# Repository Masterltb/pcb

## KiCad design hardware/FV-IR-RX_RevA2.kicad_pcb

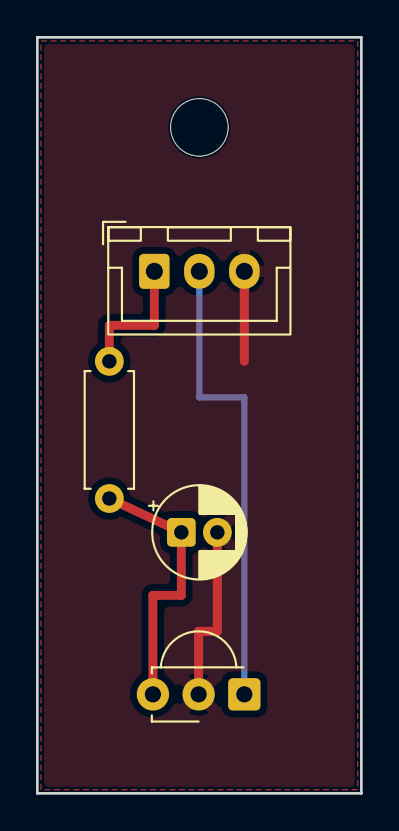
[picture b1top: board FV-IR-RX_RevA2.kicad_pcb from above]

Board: 2 copper layers, 18.0 x 42.0 mm, 5 parts (0 on the bottom side), 4 nets.

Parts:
C1: 4.7uF; CP_Radial_D5.0mm_P2.00mm
H1: MountingHole_3.2mm_M3
J1: JST_XH_3P; JST_XH_B3B-XH-A_1x03_P2.50mm_Vertical
R1: 100R; R_Axial_DIN0207_L6.3mm_D2.5mm_P7.62mm_Horizontal
U1: TSOP38238; Vishay_MINICAST-3Pin

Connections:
+3V3: J1.1, R1.1
/+3V3_FILT: C1.1, R1.2, U1.3
/IR_RX_OUT: J1.2, U1.1
GND: C1.2, J1.3, U1.2

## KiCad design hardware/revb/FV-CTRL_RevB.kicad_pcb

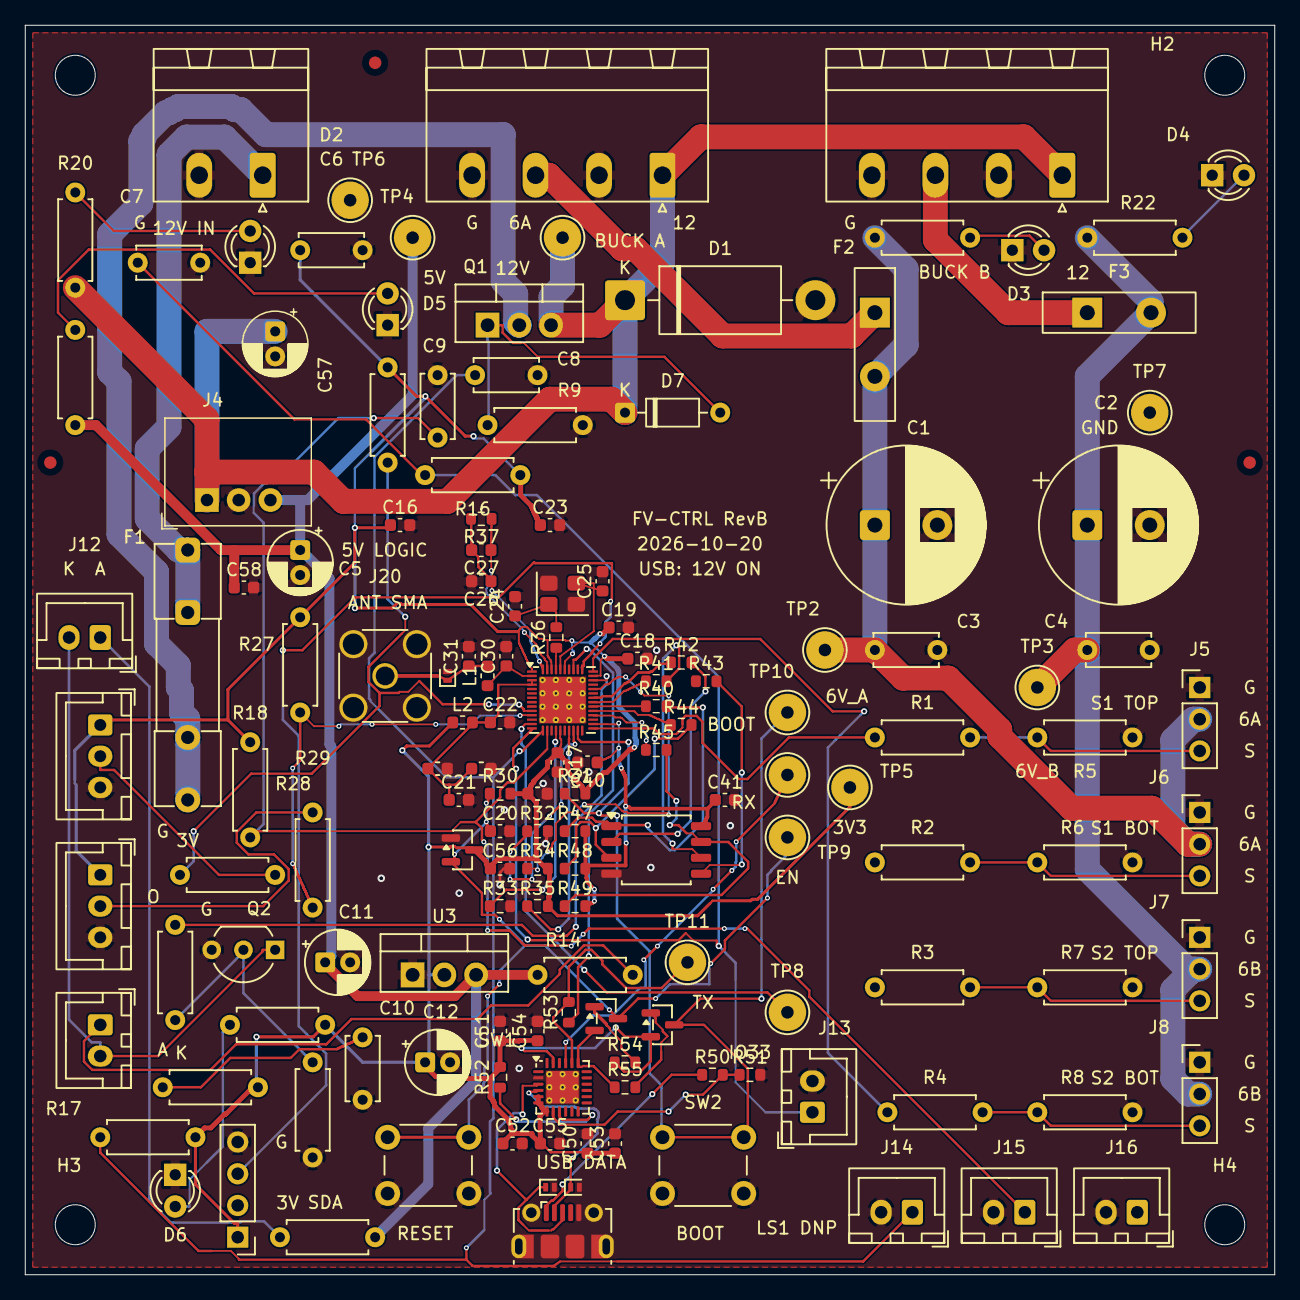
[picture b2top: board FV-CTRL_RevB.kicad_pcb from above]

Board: 2 copper layers, 100.0 x 100.0 mm, 154 parts (0 on the bottom side), 79 nets.

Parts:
C1, C2: 2200uF 16V; CP_Radial_D12.5mm_P5.00mm
C3, C4, C6, C7, C8, C9, C10: 100nF; C_Disc_D5.0mm_W2.5mm_P5.00mm
C5, C11, C12, C57: 10uF 50V; CP_Radial_D5.0mm_P2.00mm
C13, C14, C15: 10uF; C_0603_1608Metric
C16, C17, C18, C19, C22, C23, C41, C53, C54, C55, C56, C58: 100nF; C_0603_1608Metric
C20, C21, C40: 1uF; C_0603_1608Metric
C24, C25: 16pF; C_0603_1608Metric
C26: 10nF; C_0603_1608Metric
C27: 3.3nF; C_0603_1608Metric
C30: 1.5pF; C_0603_1608Metric
C31: 0.5pF; C_0603_1608Metric
C50, C51, C52: 4.7uF; C_0603_1608Metric
D1: 1.5KE15CA; D_DO-201AD_P15.24mm_Horizontal
D2: +12V; LED_D3.0mm
D3: +6V_A; LED_D3.0mm
D4: +6V_B; LED_D3.0mm
D5: +5V; LED_D3.0mm
D6: +3V3; LED_D3.0mm
D7: BZX55C12; D_DO-35_SOD27_P7.62mm_Horizontal
D8, D9, D10: PESD5V0X1BL; D_SOD-882
F1: T5A - VERIFY I2T; Fuseholder_Clip-5x20mm_Littelfuse_111_Inline_P20.00x5.00mm_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
F2, F3: MF-R300; MF_R300
FID1, FID2, FID3: Fiducial_1mm_Mask2mm
H1, H2, H3, H4: M3 MOUNT; MountingHole_3.2mm_M3
J1: 12V INPUT; PhoenixContact_MSTBA_2,5_2-G-5,08_1x02_P5.08mm_Horizontal
J2: XL4015 A: 12/G/6/G; PhoenixContact_MSTBA_2,5_4-G-5,08_1x04_P5.08mm_Horizontal
J3: XL4015 B: 12/G/6/G; PhoenixContact_MSTBA_2,5_4-G-5,08_1x04_P5.08mm_Horizontal
J4: 5V R-78E5.0-1.0; RECOM_R78E5V1A
J5: S1_TOP; PinHeader_1x03_P2.54mm_Vertical
J6: S1_BOT; PinHeader_1x03_P2.54mm_Vertical
J7: S2_TOP; PinHeader_1x03_P2.54mm_Vertical
J8: S2_BOT; PinHeader_1x03_P2.54mm_Vertical
J9: IR RX1 3V3/OUT/G; JST_XH_B3B-XH-A_1x03_P2.50mm_Vertical
J10: IR RX2 3V3/OUT/G; JST_XH_B3B-XH-A_1x03_P2.50mm_Vertical
J11: IR TX1 A/K; JST_XH_B2B-XH-A_1x02_P2.50mm_Vertical
J12: IR TX2 A/K; JST_XH_B2B-XH-A_1x02_P2.50mm_Vertical
J13: LS1 DNP; JST_XH_B2B-XH-A_1x02_P2.50mm_Vertical
J14: LS2 DNP; JST_XH_B2B-XH-A_1x02_P2.50mm_Vertical
J15: LS3 DNP; JST_XH_B2B-XH-A_1x02_P2.50mm_Vertical
J16: LS4 DNP; JST_XH_B2B-XH-A_1x02_P2.50mm_Vertical
J17: I2C 3V3/SDA/SCL/G; PinHeader_1x04_P2.54mm_Vertical
J20: SMA 50ohm ANT; SMA_Amphenol_132134_Vertical
J21: USB MICRO DATA; USB_Micro-B_Molex-105017-0001
L1: 2.7nH; L_0603_1608Metric
L2: 2.0nH; L_0603_1608Metric
Q1: IRF4905PBF; PMOS_GDS
Q2: P2N2222AG; NPN_CBE
Q3, Q4: MMBT3904; SOT-23
R1, R2, R3, R4, R13: 330R; R_Axial_DIN0207_L6.3mm_D2.5mm_P7.62mm_Horizontal
R5, R6, R7, R8, R9, R16, R17, R18, R19, R25, R26, R27: 10k; R_Axial_DIN0207_L6.3mm_D2.5mm_P7.62mm_Horizontal
R14, R15: 120R; R_Axial_DIN0207_L6.3mm_D2.5mm_P7.62mm_Horizontal
R20: 5.6k; R_Axial_DIN0207_L6.3mm_D2.5mm_P7.62mm_Horizontal
R21, R22: 2.2k; R_Axial_DIN0207_L6.3mm_D2.5mm_P7.62mm_Horizontal
R23: 1.5k; R_Axial_DIN0207_L6.3mm_D2.5mm_P7.62mm_Horizontal
R24, R28, R29: 1k; R_Axial_DIN0207_L6.3mm_D2.5mm_P7.62mm_Horizontal
R30, R31, R32, R33, R34, R35, R47, R48, R49, R54, R55: 10k; R_0603_1608Metric
R36, R40, R41, R42, R43, R44, R45: 0R; R_0603_1608Metric
R37: 20k; R_0603_1608Metric
R50: 22.1k; R_0603_1608Metric
R51: 47.5k; R_0603_1608Metric
R52: 1k; R_0603_1608Metric
R53: 499R; R_0603_1608Metric
SW1: RESET; SW_PUSH_6mm
SW2: BOOT; SW_PUSH_6mm
TP1: +12V; Keystone_5000_Carrier_D3
TP2: +6V_A; Keystone_5000_Carrier_D3
TP3: +6V_B; Keystone_5000_Carrier_D3
TP4: +5V; Keystone_5000_Carrier_D3
TP5: +3V3; Keystone_5000_Carrier_D3
TP6, TP7: GND; Keystone_5000_Carrier_D3
TP8: SPARE_GPIO33; Keystone_5000_Carrier_D3
TP9: ESP_EN; Keystone_5000_Carrier_D3
TP10: ESP_BOOT; Keystone_5000_Carrier_D3
TP11: UART_TX; Keystone_5000_Carrier_D3
TP12: UART_RX; Keystone_5000_Carrier_D3
U1: ESP32-D0WD-V3; QFN-48-1EP_5x5mm_P0.35mm_EP3.7x3.7mm_ThermalVias
U2: CP2102N-A02-GQFN24; QFN-24-1EP_4x4mm_P0.5mm_EP2.6x2.6mm_ThermalVias
U3: LD1117V33; TO-220-3_Vertical
U4: W25Q32JVSSIQ; SOIC-8_5.3x5.3mm_P1.27mm
U5: TLV803EA30DBZR; SOT-23
Y1: 40MHz CL10pF; Crystal_SMD_3225-4Pin_3.2x2.5mm

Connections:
+3V3: C6.1, C12.1, C13.1, C16.1, C17.1, C18.1, C19.1, C23.1, C50.1, C51.1, C52.1, C53.1, C54.1, C55.1, C56.1, J9.1, J10.1, J17.1, L2.1, R16.2, R17.2, R18.2, R19.2, R24.1, R26.2, R27.2, R30.2, R31.2, R34.2, R35.2, R52.2, TP5.1, U1.1, U1.19, U1.37, U1.43, U1.46, U2.5, U2.6, U2.7, U3.2, U5.3
+3V3_RF: C14.1, C15.1, C21.1, C22.1, L2.2, U1.3, U1.4
+5V: C5.1, C11.1, C58.1, J4.3, R14.1, R15.1, R23.1, TP4.1, U3.3
+6V_A: C1.1, C3.1, F2.2, J5.2, J6.2, R21.1, TP2.1
+6V_A_RAW: F2.1, J2.3
+6V_B: C2.1, C4.1, F3.2, J7.2, J8.2, R22.1, TP3.1
+6V_B_RAW: F3.1, J3.3
+12V: C57.1, D1.1, D7.1, J2.1, J3.1, J4.1, Q1.S, R20.1, TP1.1
+12V_FUSED: F1.2, Q1.D
+12V_IN: F1.1, J1.1
AUTO_BOOT_BASE: Q4.1, R55.2
AUTO_EN_BASE: Q3.1, R54.2
CAP1: C26.1, C27.2, R37.2, U1.48
CAP2: C27.1, R37.1, U1.47
ESP_BOOT: Q4.3, R31.1, SW2.1, TP10.1, U1.23
ESP_EN: C20.1, Q3.3, R30.1, SW1.1, TP9.1, U1.9, U5.2
ESP_IR_TX: R13.1, U1.36
ESP_S1_BOT_PWM: R2.1, U1.27
ESP_S1_TOP_PWM: R1.1, U1.25
ESP_S2_BOT_PWM: R4.1, U1.38
ESP_S2_TOP_PWM: R3.1, U1.35
FLASH_CLK: R41.2, U4.6
FLASH_CS: R40.2, R47.1, U4.1
FLASH_D: R43.2, U4.5
FLASH_HD: R45.2, R49.1, U4.7
FLASH_Q: R42.2, U4.2
FLASH_WP: R44.2, R48.1, U4.3
GND: C1.2, C2.2, C3.2, C4.2, C5.2, C6.2, C7.2, C8.2, C9.2, C10.2, C11.2, C12.2, C13.2, C14.2, C15.2, C16.2, C17.2, C18.2, C19.2, C20.2, C21.2, C22.2, C23.2, C24.2, C25.2, C26.2, C30.2, C31.2, C40.2, C41.2, C50.2, C51.2, C52.2, C53.2, C54.2, C55.2, C56.2, C57.2, C58.2, D1.2, D2.1, D3.1, D4.1, D5.1, D6.1, D8.2, D9.2, D10.2, J1.2, J2.2, J2.4, J3.2, J3.4, J4.2, J5.1, J6.1, J7.1, J8.1, J9.3, J10.3, J13.2, J14.2, J15.2, J16.2, J17.4, J20.2, J21.5, J21.SH, Q2.E, R5.2, R6.2, R7.2, R8.2, R9.2, R25.2, R32.2, R33.2, R51.2, SW1.2, SW2.2, TP6.1, TP7.1, U1.49, U2.2, U2.25, U3.1, U4.4, U5.1, Y1.2, Y1.4
I2C_SCL: J17.3, U1.39
I2C_SDA: J17.2, U1.42
IR_RX1: R26.1, R28.2, U1.10
IR_RX1_CABLE: J9.2, R28.1
IR_RX2: R27.1, R29.2, U1.11
IR_RX2_CABLE: J10.2, R29.1
IR_TX1_A: J11.1, R14.2
IR_TX2_A: J12.1, R15.2
IR_TX_RET: J11.2, J12.2, Q2.C
LED2_A: D2.2, R20.2
LED3_A: D3.2, R21.2
LED4_A: D4.2, R22.2
LED5_A: D5.2, R23.2
LED6_A: D6.2, R24.2
LS1: C7.1, J13.1, R16.1, U1.14
LS2: C8.1, J14.1, R17.1, U1.15
LS3: C9.1, J15.1, R18.1, U1.16
LS4: C10.1, J16.1, R19.1, U1.12
Q1_GATE: D7.2, Q1.G, R9.1
Q2_BASE: Q2.B, R13.2, R25.1
RF_50: C31.1, D8.1, J20.1, L1.2
RF_CHIP: C30.1, L1.1, U1.2
S1_BOT_PWM: J6.3, R2.2, R6.1
S1_TOP_PWM: J5.3, R1.2, R5.1
S2_BOT_PWM: J8.3, R4.2, R8.1
S2_TOP_PWM: J7.3, R3.2, R7.1
SPARE_GPIO33: TP8.1, U1.13
SPI_CLK: R41.1, U1.31
SPI_CS: R40.1, U1.30
SPI_D: R43.1, U1.33
SPI_HD: R45.1, U1.28
SPI_Q: R42.1, U1.32
SPI_WP: R44.1, U1.29
STRAP_GPIO2: R32.1, U1.22
STRAP_GPIO5: R34.1, U1.34
STRAP_GPIO12: R33.1, U1.18
STRAP_GPIO15: R35.1, U1.21
UART_RX: TP12.1, U1.40, U2.21
UART_TX: R53.2, TP11.1, U2.20
UART_TX_RAW: R53.1, U1.41
USB_DM: D10.1, J21.2, U2.4
USB_DP: D9.1, J21.3, U2.3
USB_DTR: Q4.2, R54.1, U2.23
USB_RESET: R52.1, U2.9
USB_RTS: Q3.2, R55.1, U2.19
USB_VBUS: J21.1, R50.1
USB_VBUS_SENSE: R50.2, R51.1, U2.8
VDD_SDIO: C40.1, C41.1, R47.2, R48.2, R49.2, U1.26, U4.8
XTAL_N: C25.1, U1.44, Y1.3
XTAL_P: R36.1, U1.45
XTAL_P_X: C24.1, R36.2, Y1.1
